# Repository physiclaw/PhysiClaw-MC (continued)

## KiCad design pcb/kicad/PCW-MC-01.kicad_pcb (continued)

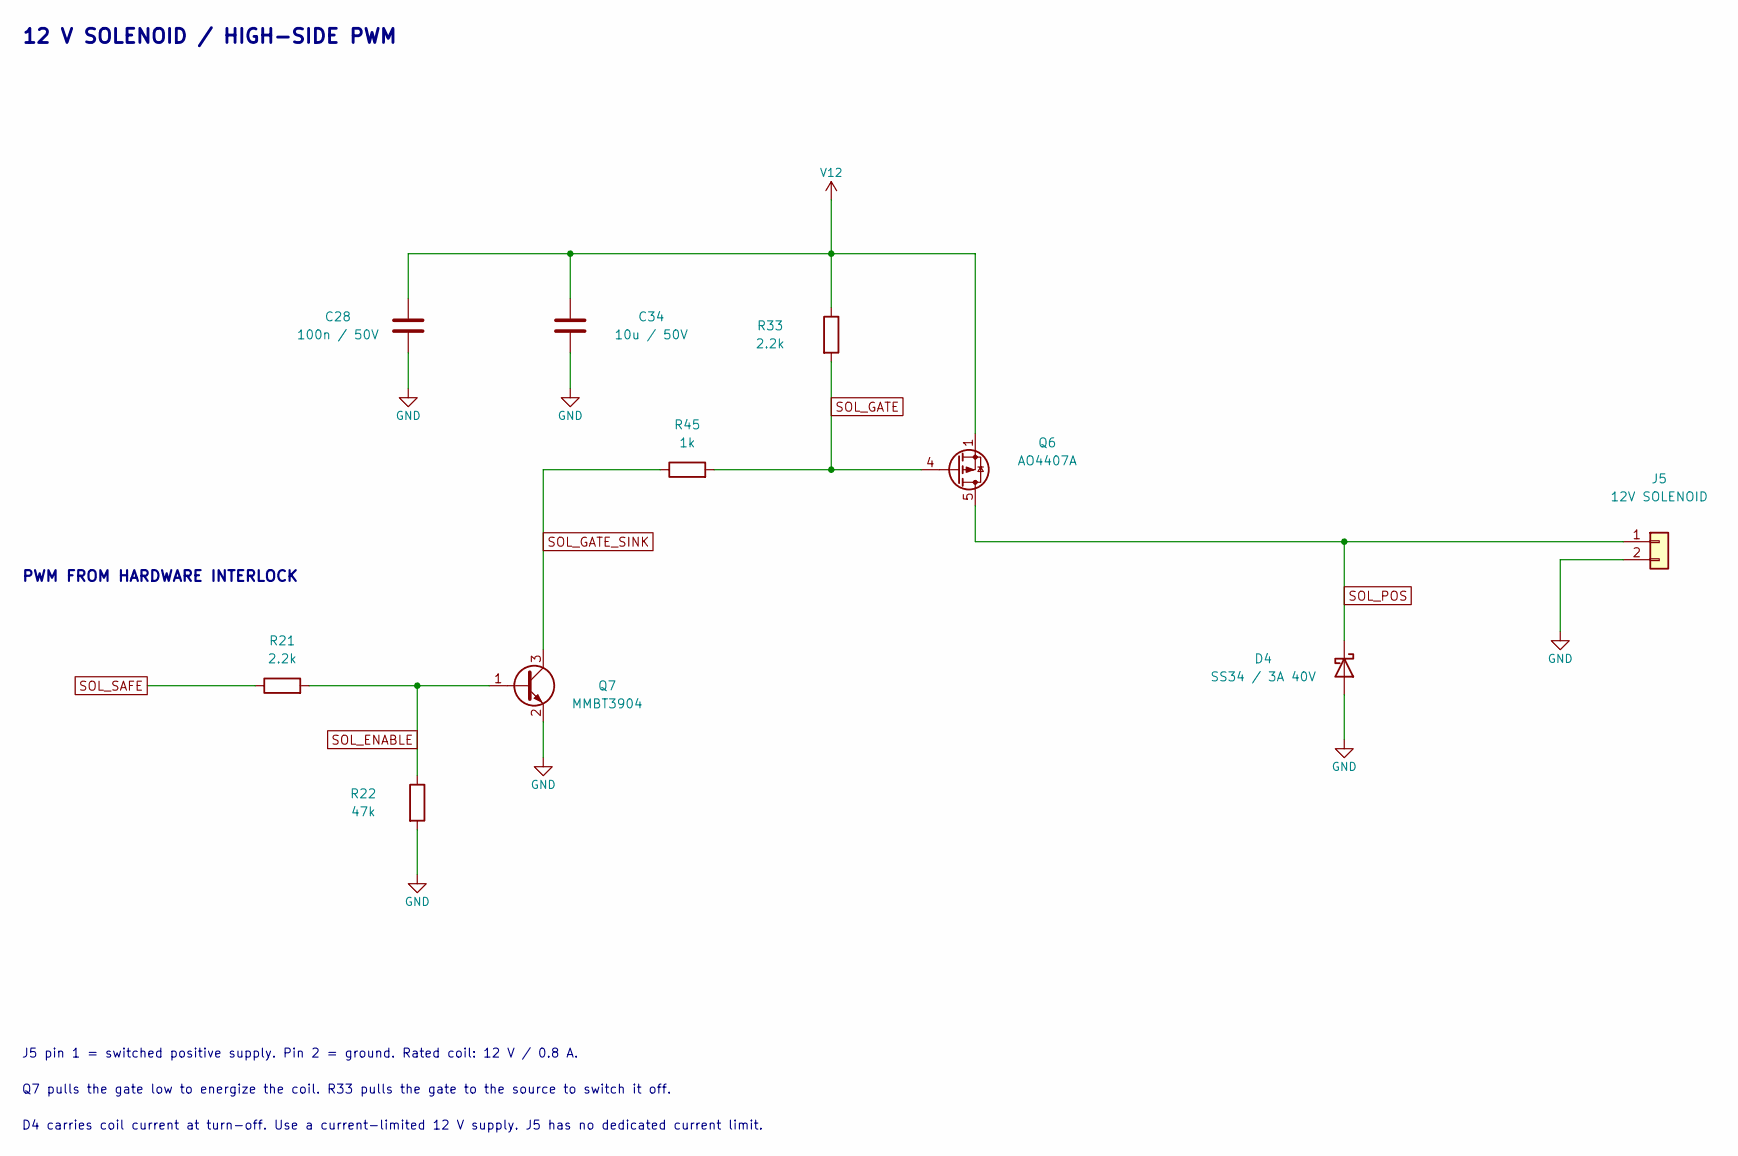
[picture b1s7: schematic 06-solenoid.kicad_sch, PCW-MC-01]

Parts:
C28: 100n / 50V; Capacitor_SMD_C_0603_1608Metric; MPN CL10B104KB8NNNC; LCSC C1591
C34: 10u / 50V; Capacitor_SMD_C_1206_3216Metric; MPN CL31B106KBHNNNE; LCSC C89632
D4: SS34 / 3A 40V; Diode_SMD_D_SMA; MPN SS34; LCSC C8678
J5: 12V SOLENOID; TerminalBlock_TerminalBlock_MaiXu_MX126-5.0-02P_1x02_P5.00mm; MPN MX126-5.0-02P-GN01-Cu-S-A; LCSC C5188434
Q6: AO4407A; Package_SO_SOIC-8_3.9x4.9mm_P1.27mm; MPN AO4407A; LCSC C2841482
Q7: MMBT3904; Package_TO_SOT_SMD_SOT-23; MPN MMBT3904; LCSC C20526
R21, R33: 2.2k; Resistor_SMD_R_0603_1608Metric; MPN 0603WAF2201T5E; LCSC C4190
R22: 47k; Resistor_SMD_R_0603_1608Metric; MPN 0603WAF4702T5E; LCSC C25819
R45: 1k; Resistor_SMD_R_0603_1608Metric; MPN 0603WAF1001T5E; LCSC C21190

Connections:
GND: C28.2, C34.2, D4.2 (A), J5.2, Q7.2 (E), R22.2; also elsewhere on the board
SOL_ENABLE: Q7.1 (B), R21.2, R22.1; also elsewhere on the board
SOL_GATE: Q6.4 (G), R33.2, R45.2
SOL_GATE_SINK: Q7.3 (C), R45.1
SOL_POS: D4.1 (K), J5.1, Q6.5 (D), Q6.6 (D), Q6.7 (D), Q6.8 (D); also elsewhere on the board
SOL_SAFE: R21.1; also elsewhere on the board
V12: C28.1, C34.1, Q6.1 (S), Q6.2 (S), Q6.3 (S), R33.1; also elsewhere on the board

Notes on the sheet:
12 V SOLENOID / HIGH-SIDE PWM
PWM FROM HARDWARE INTERLOCK
J5 pin 1 = switched positive supply. Pin 2 = ground. Rated coil: 12 V / 0.8 A.
Q7 pulls the gate low to energize the coil. R33 pulls the gate to the source to switch it off.
D4 carries coil current at turn-off. Use a current-limited 12 V supply. J5 has no dedicated current limit.

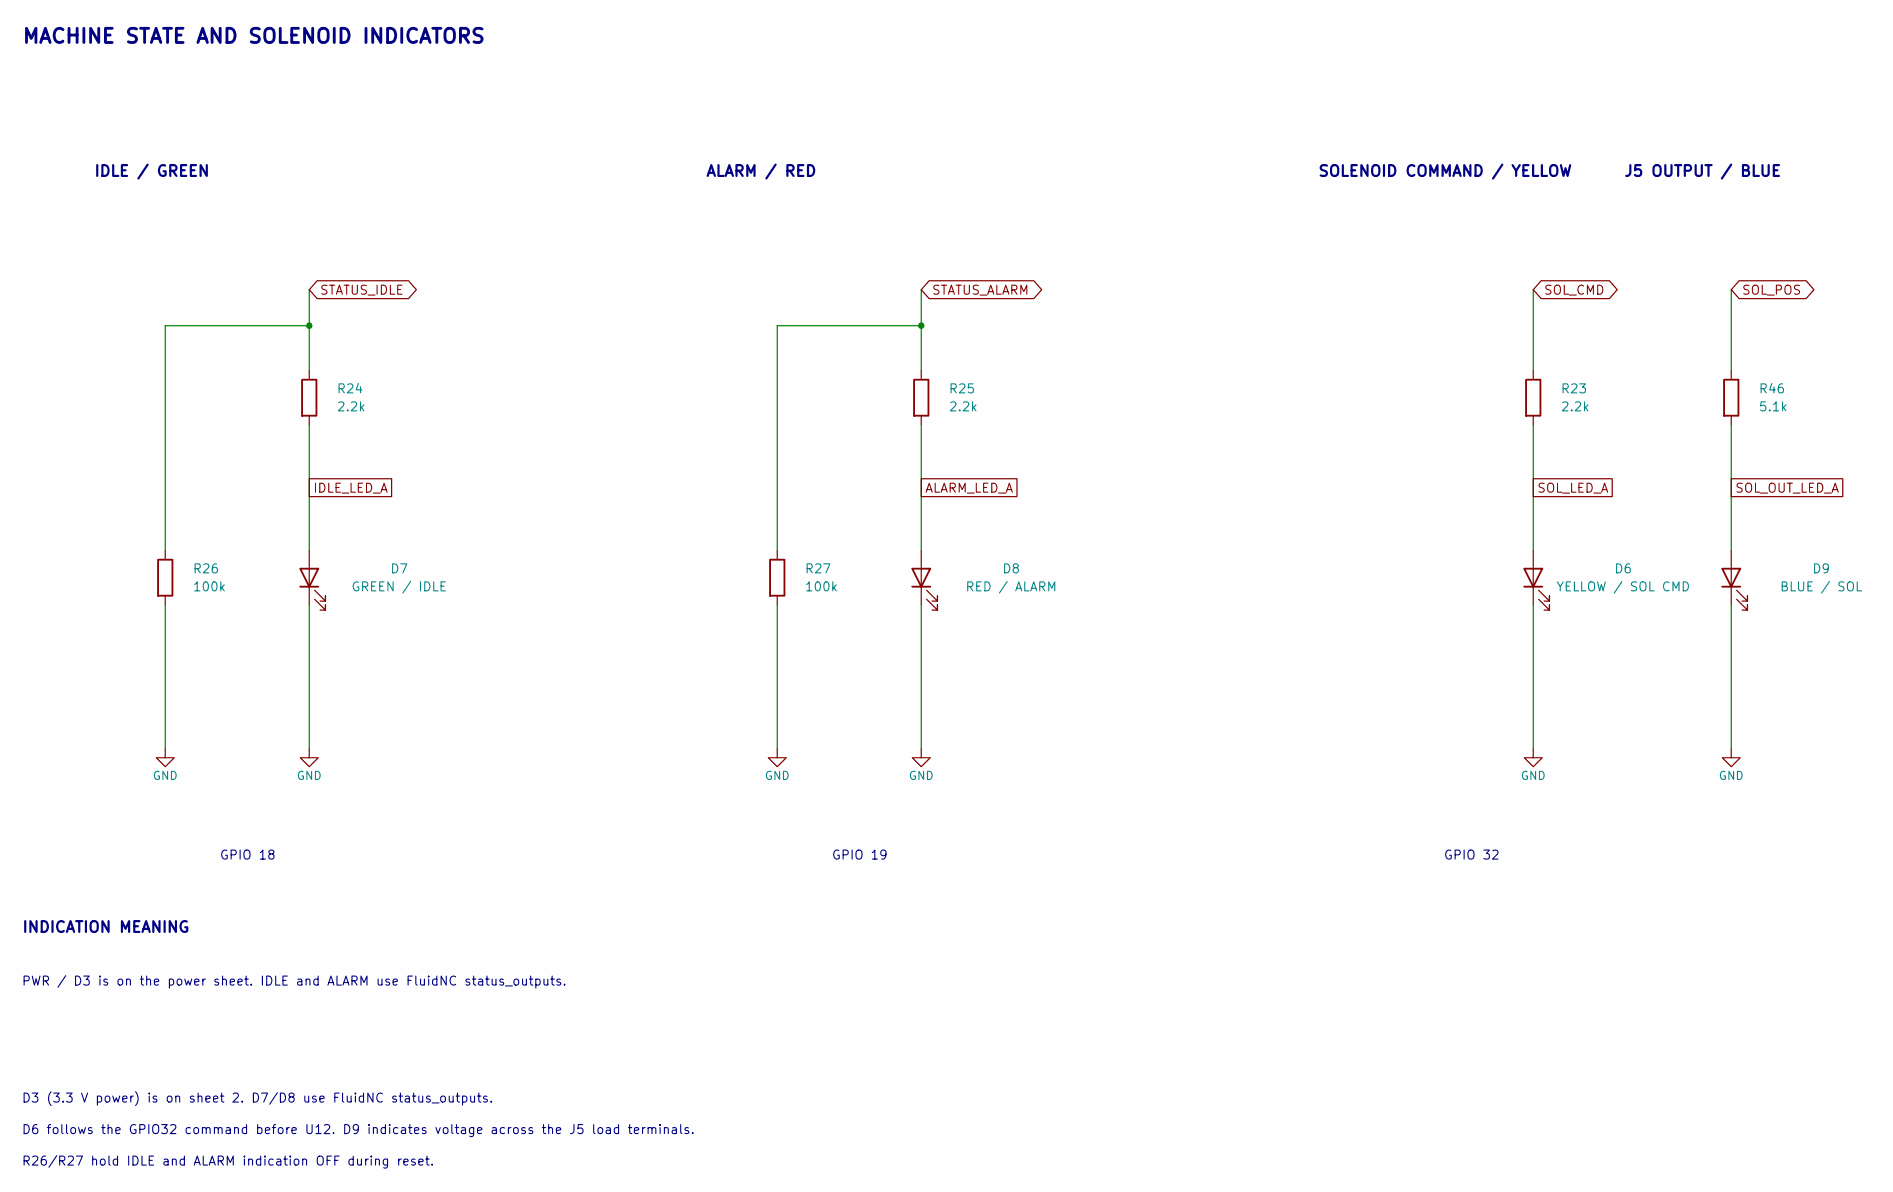
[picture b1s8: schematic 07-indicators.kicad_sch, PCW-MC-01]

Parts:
D6: YELLOW / SOL CMD; LED_SMD_LED_0603_1608Metric; MPN LTST-C190KSKT; LCSC C125095
D7: GREEN / IDLE; LED_SMD_LED_0603_1608Metric; MPN LTST-C190KGKT; LCSC C125094
D8: RED / ALARM; LED_SMD_LED_0603_1608Metric; MPN LTST-C190KRKT; LCSC C94869
D9: BLUE / SOL; LED_SMD_LED_0603_1608Metric; MPN LTST-C190TBKT; LCSC C125096
R23, R24, R25: 2.2k; Resistor_SMD_R_0603_1608Metric; MPN 0603WAF2201T5E; LCSC C4190
R26, R27: 100k; Resistor_SMD_R_0603_1608Metric; MPN 0603WAF1003T5E; LCSC C25803
R46: 5.1k; Resistor_SMD_R_0603_1608Metric; MPN 0603WAF5101T5E; LCSC C23186

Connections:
ALARM_LED_A: D8.2 (A), R25.2
GND: D6.1 (K), D7.1 (K), D8.1 (K), D9.1 (K), R26.2, R27.2; also elsewhere on the board
IDLE_LED_A: D7.2 (A), R24.2
SOL_CMD: R23.1; also elsewhere on the board
SOL_LED_A: D6.2 (A), R23.2
SOL_OUT_LED_A: D9.2 (A), R46.2
SOL_POS: R46.1; also elsewhere on the board
STATUS_ALARM: R25.1, R27.1; also elsewhere on the board
STATUS_IDLE: R24.1, R26.1; also elsewhere on the board

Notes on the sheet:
MACHINE STATE AND SOLENOID INDICATORS
IDLE / GREEN
GPIO 18
ALARM / RED
GPIO 19
SOLENOID COMMAND / YELLOW
GPIO 32
INDICATION MEANING
PWR / D3 is on the power sheet. IDLE and ALARM use FluidNC status_outputs.
D3 (3.3 V power) is on sheet 2. D7/D8 use FluidNC status_outputs.
D6 follows the GPIO32 command before U12. D9 indicates voltage across the J5 load terminals.
R26/R27 hold IDLE and ALARM indication OFF during reset.
J5 OUTPUT / BLUE

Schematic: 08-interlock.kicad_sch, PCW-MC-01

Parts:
C31, C32, C33, C39: 100n / 50V; Capacitor_SMD_C_0603_1608Metric; MPN CL10B104KB8NNNC; LCSC C1591
R31, R32, R35, R36, R37, R38: 10k; Resistor_SMD_R_0603_1608Metric; MPN 0603WAF1002T5E; LCSC C25804
R40: 820R; Resistor_SMD_R_0402_1005Metric; MPN 0402WGF8200TCE; LCSC C25135
U9, U12: SN74LVC1G125DBVR; Package_TO_SOT_SMD_SOT-23-5; MPN SN74LVC1G125DBVR; LCSC C23654
U10: SN74LVC1G132DBVR; Package_TO_SOT_SMD_SOT-23-5; MPN SN74LVC1G132DBVR; LCSC C403723
U11: TLV803EA30DBZR; Package_TO_SOT_SMD_SOT-23; MPN TLV803EA30DBZR; LCSC C5218924

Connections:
ACTUATOR_ARM: R35.1, U10.2 (B); also elsewhere on the board
ACT_OE_N: R36.2, U9.1, U10.4 (Y), U12.1; also elsewhere on the board
DRIVERS_DISABLE: U9.4; also elsewhere on the board
DRV_DISABLE_CMD: R37.2, U9.2; also elsewhere on the board
ESP_EN: R40.2, U10.1 (A); also elsewhere on the board
GND: C31.2, C32.2, C33.2, C39.2, R31.2, R32.2, R35.2, R38.2, U9.3 (GND), U10.3 (GND), U11.1 (GND), U12.3 (GND); also elsewhere on the board
RESET_SINK: R40.1, U11.2 (~RESET)
SOL_CMD: R38.1, U12.2; also elsewhere on the board
SOL_SAFE: U12.4; also elsewhere on the board
V3V3: C31.1, C32.1, C33.1, C39.1, R36.1, R37.1, U9.5 (VCC), U10.5 (VCC), U11.3 (VDD), U12.5 (VCC); also elsewhere on the board
X_STEP: R31.1; also elsewhere on the board
Y_STEP: R32.1; also elsewhere on the board

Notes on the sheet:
ACTUATOR INHIBIT, SUPPLY SUPERVISOR AND DEFINED STEP INPUTS
ARM HIGH and ESP_EN HIGH make ACT_OE_N LOW: U9 passes motor disable and U12 passes solenoid PWM.
Otherwise U9 and U12 are high impedance. R9 disables the motors and R22 holds Q7 off.
U11: 3.08 V threshold, 200 ms nominal release. R40 limits reset sink current.
On normal boot, FluidNC turns both outputs off, then raises ARM.
ARM / RESET QUALIFICATION
ACTUATOR COMMAND BUFFERS
RESET SUPERVISOR
LOCAL BYPASS / U9, U12, U10, U11
OE LOW: commands pass
OE HIGH: outputs float
Motor / solenoid defaults: sheet 3 / 7

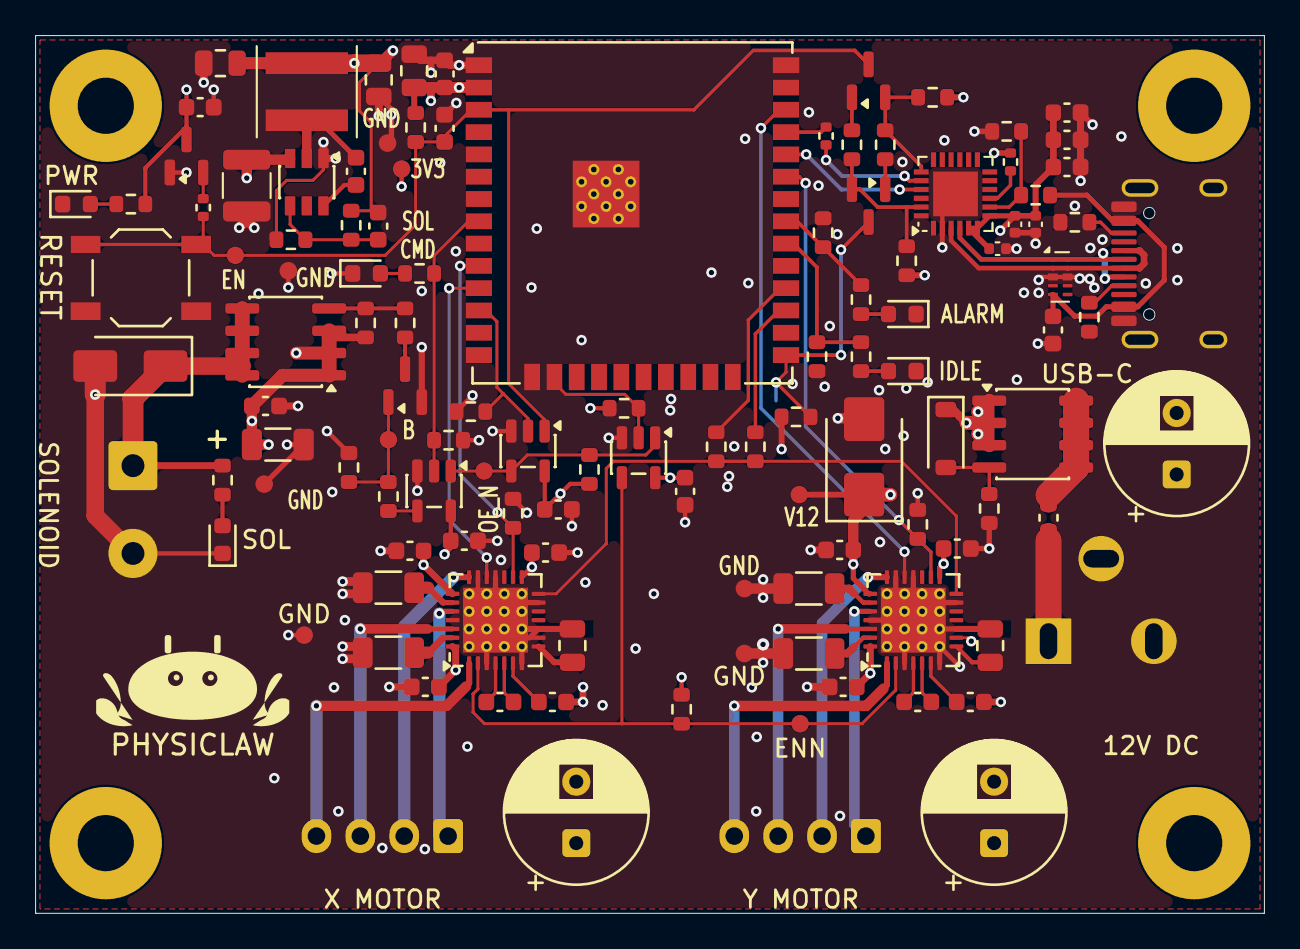
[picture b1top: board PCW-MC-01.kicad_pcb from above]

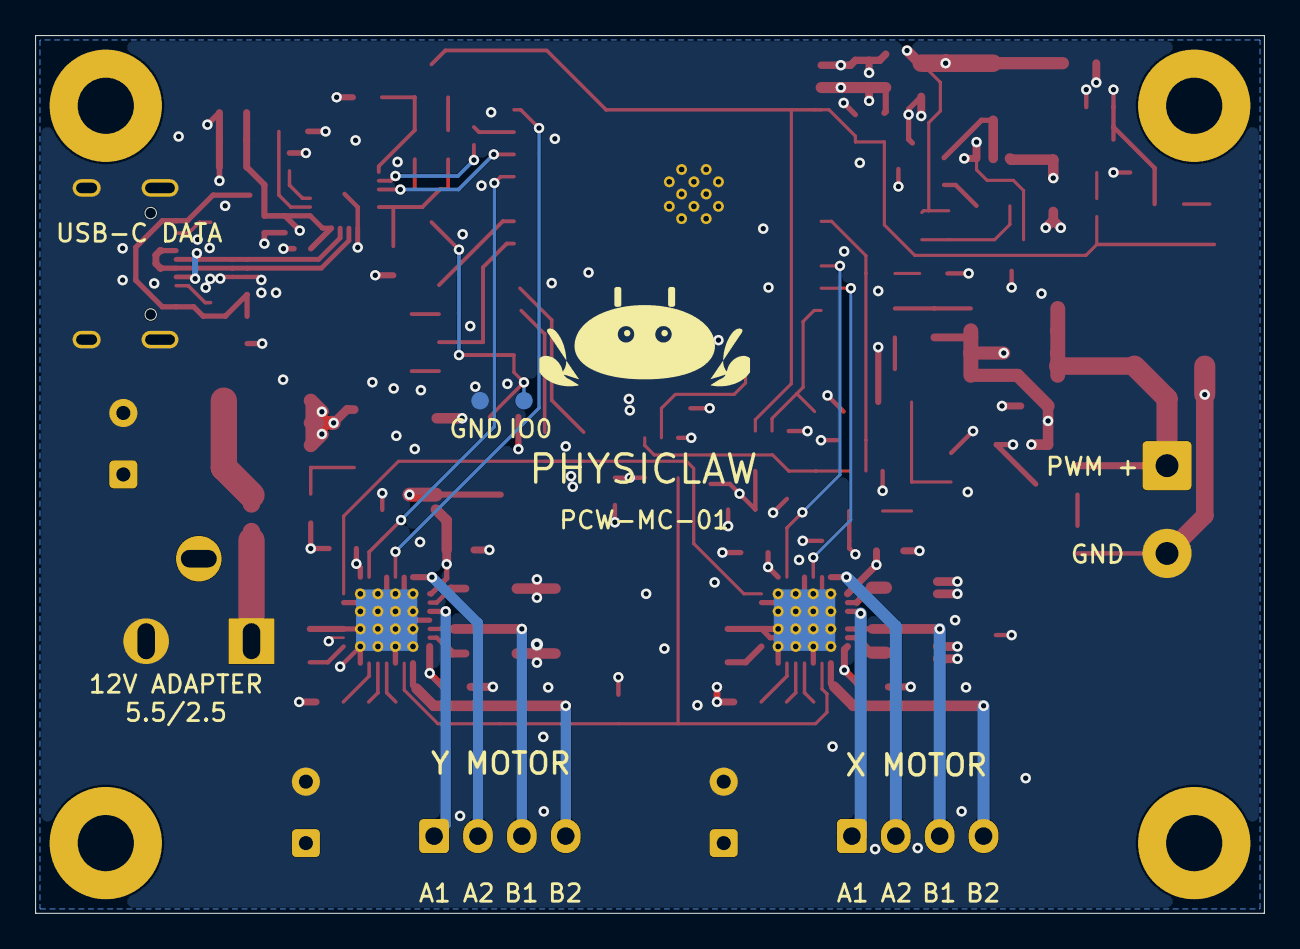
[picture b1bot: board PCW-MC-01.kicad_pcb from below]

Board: 4 copper layers, 70.0 x 50.0 mm, 125 parts (2 on the bottom side), 70 nets.

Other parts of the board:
H1, H2, H3, H4: M3 isolated plated mounting hole; MountingHole_3.2mm_M3_Pad
TP1: IO0 recovery; TestPoint_Pad_D1.0mm
TP2: GND recovery; TestPoint_Pad_D1.0mm
TP3: 3V3; TestPoint_Pad_D1.0mm_Compact
TP4, TP15: GND; TestPoint_Pad_D1.0mm_Compact
TP5: ENN; TestPoint_Pad_D1.0mm
TP6, TP8, TP11, TP13: GND; TestPoint_Pad_D1.0mm
TP9: EN; TestPoint_Pad_D1.0mm
TP10: V12; TestPoint_Pad_D1.0mm
TP12: OE_N; TestPoint_Pad_D1.0mm_Compact
TP14: B; TestPoint_Pad_D1.0mm_Compact

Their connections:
ACT_OE_N: TP12.1; also elsewhere on the board
BOOT_N: TP1.1; also elsewhere on the board
DRIVERS_DISABLE: TP5.1; also elsewhere on the board
ESP_EN: TP9.1; also elsewhere on the board
GND: TP2.1, TP4.1, TP6.1, TP8.1, TP11.1, TP13.1, TP15.1; also elsewhere on the board
SOL_ENABLE: TP14.1; also elsewhere on the board
V3V3: TP3.1; also elsewhere on the board
V12: TP10.1; also elsewhere on the board

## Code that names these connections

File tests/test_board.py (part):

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    def test_rear_recovery_probes(self):
        io, ground = (self.footprints[ref].pads[0] for ref in ("TP1", "TP2"))
        self.assertAlmostEqual(math.dist(io.xy, ground.xy), 2.5)
        for probe, net, label in ((io, "BOOT_N", "IO0"), (ground, "GND", "GND")):
            self.assertEqual(probe.net, net)
            self.assertTrue(probe.on_layer("B.Cu"))
            self.assertFalse(probe.on_layer("F.Cu"))
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                ), limit)

    def test_reverse_polarity_gate_clamp_reaches_both_mosfet_pins_on_top(self):
        for net, diode_pin, mosfet_pin in (("V12", "1", "2"), ("REV_GATE", "2", "4")):
            with self.subTest(net=net):
                diode = ("F.Cu", pad_center(self.footprints["D1"], diode_pin))
                mosfet = ("F.Cu", pad_center(self.footprints["Q1"], mosfet_pin))
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        bridge = nets("U4")
        self.assertEqual(self.footprints["U4"].fields["MPN"], "CP2102N-A02-GQFN24R")
        for pin in ("5", "6", "7"):
            self.assertEqual(bridge[pin], "V3V3")
        for pin in ("2", "25"):
            self.assertEqual(bridge[pin], "GND")
        self.assertEqual((bridge["19"], bridge["20"], bridge["21"], bridge["23"]),
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
    def test_x_driver_shunt_paths_match_at_each_track_width(self):
        paths = []
        for net, pin, resistor in (("X_SENSE_A", "23", "R17"), ("X_SENSE_B", "27", "R18")):
            by_width = defaultdict(float)
            for track in self.segments["F.Cu", net]:
                width, = values(track, "width")
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                                       math.dist(output[1], anode.xy))

    def test_bridge_uart_uses_one_bottom_run_between_two_short_top_fanouts(self):
        for net, ref, pin, bridge_pin in (("ESP_TX", "R28", "2", "20"), ("ESP_RX", "U2", "34", "21")):
            with self.subTest(net=net):
                vias = self.through_via_positions(net)
                self.assertEqual(len(vias), 2)
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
